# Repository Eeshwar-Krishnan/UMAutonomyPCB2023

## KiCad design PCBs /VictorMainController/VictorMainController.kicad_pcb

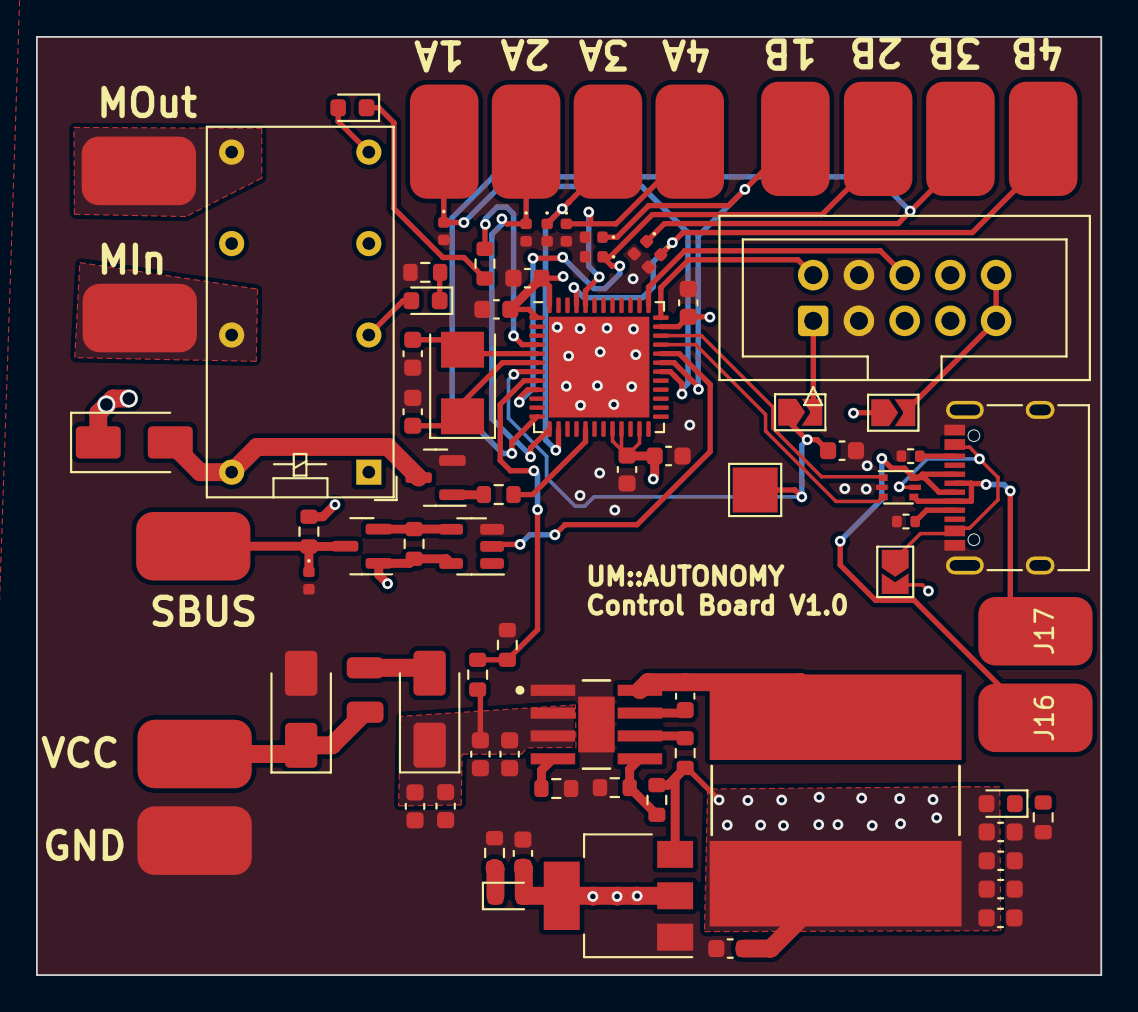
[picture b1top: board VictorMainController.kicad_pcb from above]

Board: 4 copper layers, 59.1 x 52.1 mm, 82 parts (0 on the bottom side), 48 nets.

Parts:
C1, C2, C3, C4, C12, C13, C14, C15, C16: 4.7u; C_0603_1608Metric
C5: 100n; C_0603_1608Metric
C6, C7, C8, C9, C10, C11: 47u; C_0603_1608Metric
C17, C18: 20pf; C_0603_1608Metric
C19: 0.1u; C_0603_1608Metric
D1: SMAJ75CA; D_SMA
D2, D14: SS310; D_SMA
D3: 5VGood; LED_0603_1608Metric
D4, D5, D6, D7, D8, D9, D10, D11, D16: RCLAMP0521P-N; D_0402_1005Metric
D12: 3V3Good; LED_0603_1608Metric
D13: Status1; LED_0603_1608Metric
D15: LED_Small; LED_0603_1608Metric
F1: 0458002.DR
J1, J3, J4, J5, J6, J7, J8, J9, J10, J11, J13, J14, J15, J16, J17: Conn_01x01_Pin; SOLDERPAD_150x250
J2: USB_C_Receptacle_USB2.0; USB_C_Receptacle_XKB_U262-16XN-4BVC11
J12: Conn_02x05_Odd_Even; IDC-Header_2x05_P2.54mm_Vertical
JP1: NRST; SolderJumper-2_P1.3mm_Open_TrianglePad1.0x1.5mm
JP2, JP3: SolderJumper_2_Open; SolderJumper-2_P1.3mm_Open_TrianglePad1.0x1.5mm
K1: G5V-2; Relay_DPDT_Omron_G5V-2
L1: 15u; IND_BOURNS_SDR1307
Q1: BSS138; SOT-23
Q2: 2N7002; SOT-23
R1: 64.9k; R_0603_1608Metric
R2: 100k; R_0603_1608Metric
R3: 40.2k; R_0603_1608Metric
R4, R7, R13: 10k; R_0603_1608Metric
R5: 30900; R_0603_1608Metric
R6: 1180; R_0603_1608Metric
R8: 220; R_0603_1608Metric
R9, R10: 5.1k; R_0402_1005Metric
R11: 137; R_0603_1608Metric
R12, R15: 68.1; R_0603_1608Metric
R14: 330; R_0603_1608Metric
TP1: TestPoint; TestPoint_Pad_2.5x2.5mm
U1: PLMR38020FDDAR; DDA0008E-IPC_A
U2: AMS1117-3.3; SOT-223-3_TabPin2
U3: STM32G431CBUx; QFN-48-1EP_7x7mm_P0.5mm_EP5.6x5.6mm
U4: SN74LVC1G14DBV; SOT-23-5
U5: USBLC6-2P6; SOT-666
Y1: X50328MSB2GI; Crystal_SMD_5032-2Pin_5.0x3.2mm

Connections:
+3V3: C11.1, C12.1, C13.1, C14.1, C15.1, C16.1, D12.2 (A), D13.2 (A), K1.8, Q1.1 (G), R7.2, U2.2 (VO), U3.1 (VBAT), U3.20 (VREF+), U3.21 (VDDA), U3.23 (VDD), U3.35 (VDD), U3.48 (VDD), U4.5 (VCC)
+5V: C6.1, C7.1, C8.1, C9.1, C10.1, D3.2 (A), D14.1 (K), JP2.2 (B), JP3.1 (A), K1.1, L1.2, R2.2, R3.1, R13.2, U2.3 (VI)
/MCU/SBUS_INV: U3.32 (PA10), U4.2
/M_EN: R14.1, U3.17 (PB0)
/MotorIN: J13.1, K1.13
/MotorOUT: J14.1, K1.9
/NRST: C19.1, JP1.1 (A), TP1.1, U3.7 (PG10)
/PWM1A: D4.1 (K), J4.1, U3.30 (PA8)
/PWM1B: D5.1 (K), J5.1, U3.31 (PA9)
/PWM2A: D6.1 (K), J6.1, U3.13 (PA5)
/PWM2B: D7.1 (K), J7.1, U3.9 (PA1)
/PWM3A: D8.1 (K), J8.1, U3.14 (PA6)
/PWM3B: D9.1 (K), J9.1, U3.12 (PA4)
/PWM4A: D10.1 (K), J10.1, U3.44 (PB6)
/PWM4B: D11.1 (K), J11.1, U3.45 (PB7)
/SBUS: Q1.2 (S), R7.1, U4.4
/SBUS_5V: D16.1 (K), J15.1, Q1.3 (D), R13.1
/SWCLK: J12.6, U3.37 (PA14)
/SWDIO: J12.2, U3.36 (PA13)
/USBDM: U3.33 (PA11), U5.3 (I/O2)
/USBDMR: J2.A7 (D-), J2.B7 (D-), J17.1, U5.4 (I/O2)
/USBDP: U3.34 (PA12), U5.1 (I/O1)
/USBDPR: J2.A6 (D+), J2.B6 (D+), J16.1, U5.6 (I/O1)
/USBVCC: J2.A4 (VBUS), J2.A9 (VBUS), J2.B4 (VBUS), J2.B9 (VBUS), JP2.1 (A), U5.5 (VBUS)
/VSense: R5.2, R6.1, U3.8 (PA0)
GND: C1.1, C2.1, C3.1, C4.1, C6.2, C7.2, C8.2, C9.2, C10.2, C11.2, C12.2, C13.2, C14.2, C15.2, C16.2, C17.2, C18.2, C19.2, D1.2 (A), D4.2 (A), D5.2 (A), D6.2 (A), D7.2 (A), D8.2 (A), D9.2 (A), D10.2 (A), D11.2 (A), D16.2 (A), J2.A1 (GND), J2.A12 (GND), J2.B1 (GND), J2.B12 (GND), J2.S1 (SHIELD), J3.1, J12.3, J12.4, Q2.2 (S), R1.2, R4.2, R6.2, R9.2, R10.2, R11.2, R12.2, R15.2, U1.1 (PGND), U1.9 (EP), U2.1 (GND), U3.49 (VSS), U4.3 (GND), U5.2 (GND)
unnamed: D1.1 (K), F1.1, J1.1
unnamed: D2.2 (A), F1.2
unnamed: D3.1 (K), R11.1
unnamed: D12.1 (K), R12.1
unnamed: D13.1 (K), R8.1
unnamed: D14.2 (A), K1.16, Q2.3 (D)
unnamed: D15.2 (A), K1.4
unnamed: D15.1 (K), R15.1
unnamed: J2.A5 (CC1), R10.1
unnamed: J2.B5 (CC2), R9.1
unnamed: J12.1, JP1.2 (B)
unnamed: J12.9, J12.10, JP3.2 (B)
unnamed: Q2.1 (G), R14.2
unnamed: C5.2, U1.7 (BOOT)
unnamed: R3.2, R4.1, U1.5 (FB)
unnamed: R2.1, U1.6 (PG)
unnamed: R1.1, U1.4 (RT_SYNC)
unnamed: C5.1, L1.1, U1.8 (SW)
unnamed: R8.2, U3.4 (PC15)
unnamed: C18.1, U3.5 (PF0), Y1.2
unnamed: C17.1, U3.6 (PF1), Y1.1
VCC: C1.2, C2.2, C3.2, C4.2, D2.1 (K), R5.1, U1.2 (EN), U1.3 (VIN)

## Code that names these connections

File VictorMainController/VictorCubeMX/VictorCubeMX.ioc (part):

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Mcu.Name=STM32G431C(6-8-B)Ux
Mcu.Package=UFQFPN48
Mcu.UserName=STM32G431CBUx
PA0.Mode=IN1-Single-Ended
PA0.Signal=ADC1_IN1
PA1.Signal=S_TIM2_CH2
PA10.Mode=Asynchronous
PA10.Signal=USART1_RX
PA11.Mode=Device
PA11.Signal=USB_DM
PA12.Mode=Device
PA12.Signal=USB_DP
PA13.Mode=JTAG_4_pins
PA13.Signal=SYS_JTMS-SWDIO
PA14.Mode=JTAG_4_pins
PA14.Signal=SYS_JTCK-SWCLK
PA15.Mode=JTAG_4_pins
PA15.Signal=SYS_JTDI
PA4.Signal=S_TIM3_CH2
PA5.Signal=S_TIM2_CH1
PA6.Signal=S_TIM3_CH1
PA8.Signal=S_TIM1_CH1
PA9.Signal=S_TIM1_CH2
PB3.Mode=JTAG_4_pins
PB3.Signal=SYS_JTDO-SWO
PB6.Signal=S_TIM4_CH1
PB7.Signal=S_TIM4_CH2
PC4.Mode=Asynchronous
PC4.Signal=USART1_TX
RCC.HSE_VALUE=8000000
RCC.SYSCLKFreq_VALUE=16000000
board=custom

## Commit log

2023-09-10 first
